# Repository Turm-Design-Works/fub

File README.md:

# fub.*~
**Pocket MIDI interface for Foot Switch &amp; Expression Pedal**  
  
Type-C :  
> to HOST

6.35 jack × 4 :  
> LEFT 2 jacks | Foot Switch jack. (Dual Foot Switch is available.)  
> RIGHT 2 jacks | Expression Pedal jack.

DIN 5pin × 1 :  
> MIDI OUT. This outputs MIDI datas of Foot SWs&Pedals and Note,CC,etc from Host.  

It is using ATSAND21G18A microcom chip as core.  

# LICENSES  
**MIT** ( [view LICENSE](https://github.com/Turm-Design-Works/fub/blob/main/LICENSE) )  
2024 Turm Design Works LLC.

# How to install firmware  
It needs to install "microchip(Atmel) studio", and prepare SAM/ARM writer (e. Atmel ICE, PICkit, j-link) with 5 debug wires.  
  
1. Solder all parts.
2. Connect fub.*~ & SAM/ARM writer to your PC.
3. Connect writer to fub.*~ PCB empty holes is marked "R V G C D" by using debug wire.  
> R: RESET, V: VTG 3.3V, G: GND, C: SWCLK, D: SWDIO  
> Please follow the connection of writer outputs you use.  
>   
4. Open microchip studio application.
> Move to "Tools" -> "Device Programming".  
>   
5. Apply writer and read chip.
> 1: Select writer you use, 2: Select Device "ATSAMD21G18A", 3: Select Interface "SWD",  
> 4: Click "Apply", 5: Click "Read"  
>   
6. Move to memories tab, program .hex firmware.
> 1: Click "Erase now", 2: Select fub_boot_v.v.v.v.hex firmware, 3: Click "Program"
>   
7. Disconnect fub.*~ and ARM writer from PC, and disconnect debug wire. Done.

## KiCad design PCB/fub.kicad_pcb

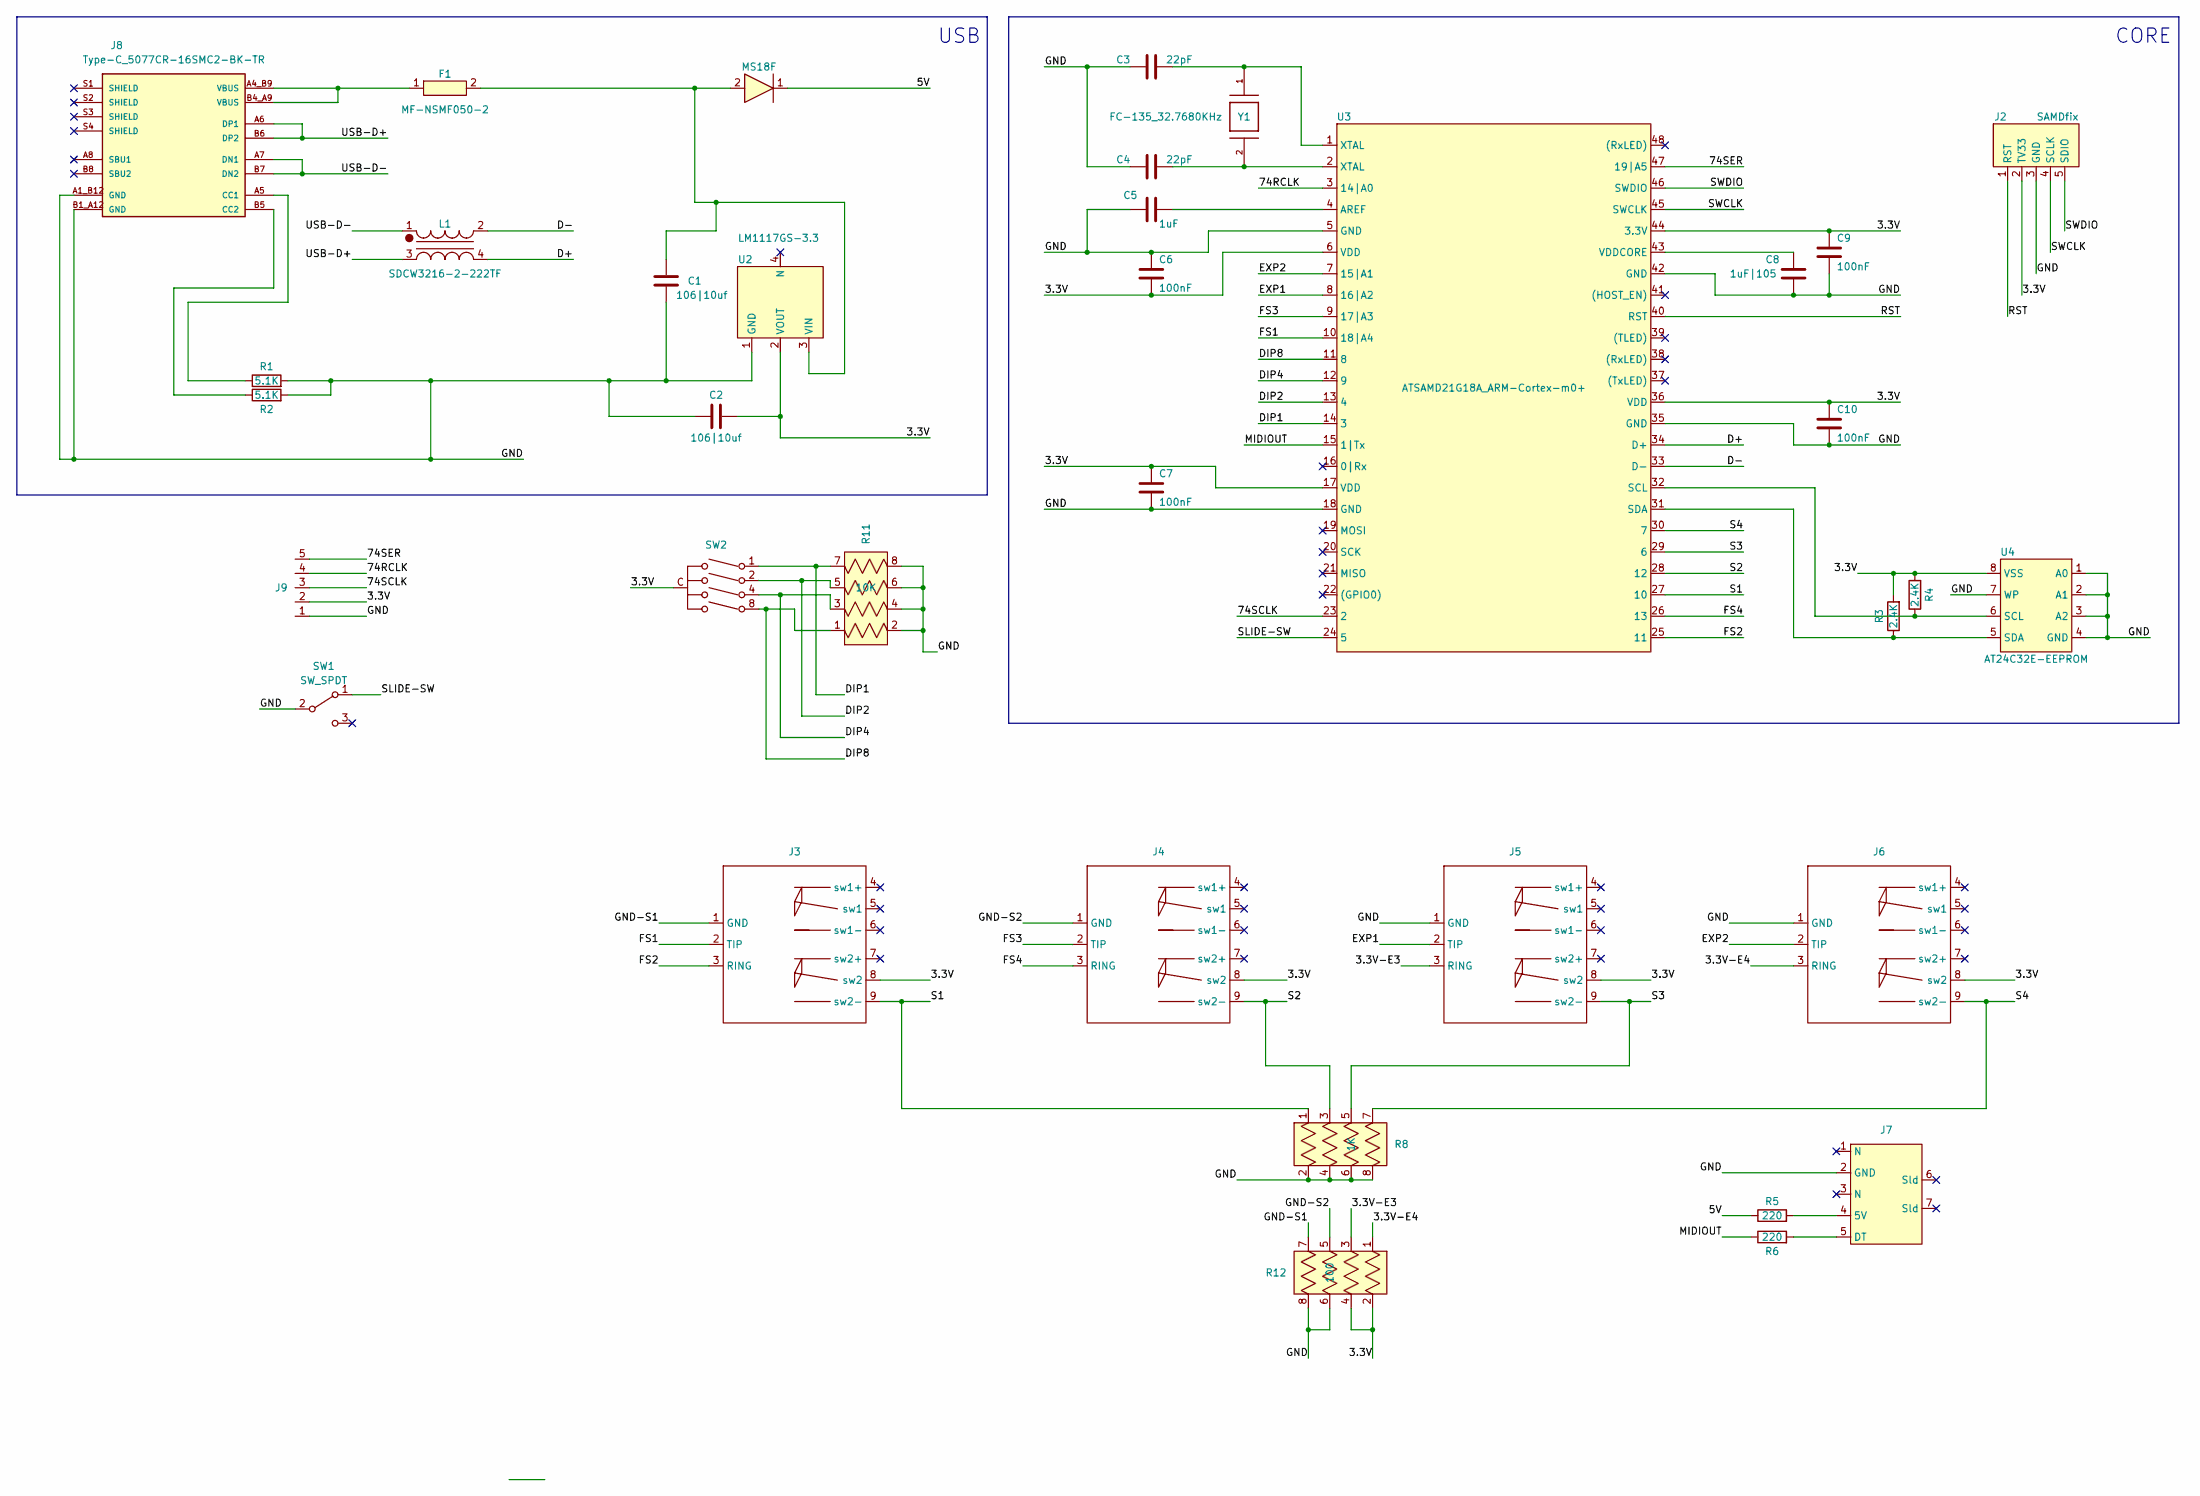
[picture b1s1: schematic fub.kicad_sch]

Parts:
C1, C2: 106|10uf; C_0603_1608Metric
C3, C4: 22pF; C_0603_1608Metric
C5: 1uF; C_0603_1608Metric
C6, C7, C9, C10: 100nF; C_0603_1608Metric
C8: 1uF|105; C_0603_1608Metric
F1: MF-NSMF050-2; MF-NSMF
J2: SAMDfix; 5tht
J3, J4, J5, J6: MJ-188LPD-8C
J7: KDJ03-5_MIDI
J8: Type-C_5077CR-16SMC2-BK-TR; NELTRON_5077CR-16SMC2-BK-TR
J9: 5ZH
L1: SDCW3216-2-222TF
R1, R2: 5.1K; R_0603_1608Metric
R3, R4: 2.4K; R_0603_1608Metric
R5, R6: 220; R_0603_1608Metric
R8: 1K; BCN164AB221J7
R11: 10K; MNR04M0ABJ103_register-arrray-small
R12: 100; BCN164AB221J7
SW1: SW_SPDT; SS-12D01G3_SLIDE-SW
SW2: FR01_dip-rotary16
U1: MS18F; MS18F_BARRIER
U2: LM1117GS-3.3; SOT-223
U3: ATSAMD21G18A_ARM-Cortex-m0+; QFP50P900X900X120-48N
U4: AT24C32E-EEPROM; SOIC-8_3.9x4.9mm_P1.27mm
Y1: FC-135_32.7680KHz; XTAL_FC-135_32.7680KA-A0

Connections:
/3.3V: C2.2, C6.1, C7.2, C9.2, C10.2, J2.2 (TV33), J3.8 (sw2), J4.8 (sw2), J5.8 (sw2), J6.8 (sw2), J9.2, R3.2, R4.2, R12.2, R12.4, SW2.C, U2.2 (VOUT), U3.6 (VDD), U3.17 (VDD), U3.36 (VDD), U3.44 (3.3V), U4.8 (VSS)
/3.3V-E3: J5.3 (RING), R12.3
/3.3V-E4: J6.3 (RING), R12.1
/5V: R5.1, U1.1
/74RCLK: J9.4, U3.3 (14|A0)
/74SCLK: J9.3, U3.23 (2)
/74SER: J9.5, U3.47 (19|A5)
/D+: L1.4, U3.34 (D+)
/D-: L1.2, U3.33 (D-)
/DIP1: R11.7, SW2.1, U3.14 (3)
/DIP2: R11.5, SW2.2, U3.13 (4)
/DIP4: R11.3, SW2.4, U3.12 (9)
/DIP8: R11.1, SW2.8, U3.11 (8)
/EXP1: J5.2 (TIP), U3.8 (16|A2)
/EXP2: J6.2 (TIP), U3.7 (15|A1)
/FS1: J3.2 (TIP), U3.10 (18|A4)
/FS2: J3.3 (RING), U3.25 (11)
/FS3: J4.2 (TIP), U3.9 (17|A3)
/FS4: J4.3 (RING), U3.26 (13)
/GND: C1.2, C2.1, C3.2, C4.2, C5.2, C6.2, C7.1, C8.1, C9.1, C10.1, J2.3 (GND), J5.1 (GND), J6.1 (GND), J7.2 (GND), J8.A1_B12 (GND), J8.B1_A12 (GND), J9.1, R1.2, R2.2, R8.2, R8.4, R8.6, R8.8, R11.2, R11.4, R11.6, R11.8, R12.6, R12.8, SW1.2 (B), U2.1 (GND), U3.5 (GND), U3.18 (GND), U3.35 (GND), U3.42 (GND), U4.1 (A0), U4.2 (A1), U4.3 (A2), U4.4 (GND), U4.7 (WP)
/GND-S1: J3.1 (GND), R12.7
/GND-S2: J4.1 (GND), R12.5
/MIDIOUT: R6.1, U3.15 (1|Tx)
/RST: J2.1 (RST), U3.40 (RST)
/S1: J3.9 (sw2-), R8.1, U3.27 (10)
/S2: J4.9 (sw2-), R8.3, U3.28 (12)
/S3: J5.9 (sw2-), R8.5, U3.29 (6)
/S4: J6.9 (sw2-), R8.7, U3.30 (7)
/SLIDE-SW: SW1.1 (A), U3.24 (5)
/SWCLK: J2.4 (SCLK), U3.45 (SWCLK)
/SWDIO: J2.5 (SDIO), U3.46 (SWDIO)
/USB-D+: J8.A6 (DP1), J8.B6 (DP2), L1.3
/USB-D-: J8.A7 (DN1), J8.B7 (DN2), L1.1
unnamed: C3.1, U3.1 (XTAL), Y1.1
unnamed: C4.1, U3.2 (XTAL), Y1.2
unnamed: F1.1, J8.A4_B9 (VBUS), J8.B4_A9 (VBUS)
unnamed: J7.4 (5V), R5.2
unnamed: J7.5 (DT), R6.2
unnamed: J8.A5 (CC1), R1.1
unnamed: J8.B5 (CC2), R2.1
unnamed: C1.1, F1.2, U1.2, U2.3 (VIN)
unnamed: C5.1, U3.4 (AREF)
unnamed: R4.1, U3.32 (SCL), U4.6 (SCL)
unnamed: R3.1, U3.31 (SDA), U4.5 (SDA)
unnamed: C8.2, U3.43 (VDDCORE)

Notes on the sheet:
CORE
USB

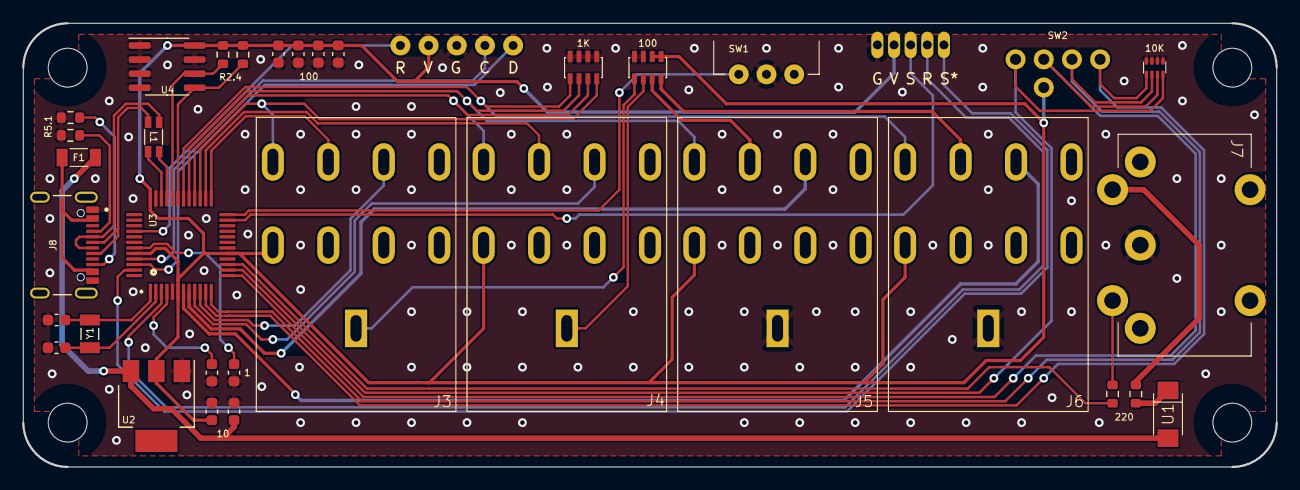
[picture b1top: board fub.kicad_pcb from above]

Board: 2 copper layers, 113.0 x 40.0 mm, 36 parts (0 on the bottom side), 45 nets.

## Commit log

2024-05-22 Create assemblypartslist
2024-05-23 Update assemblypartslist

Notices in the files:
PCB/fub.kicad_pcb:
License : MIT
